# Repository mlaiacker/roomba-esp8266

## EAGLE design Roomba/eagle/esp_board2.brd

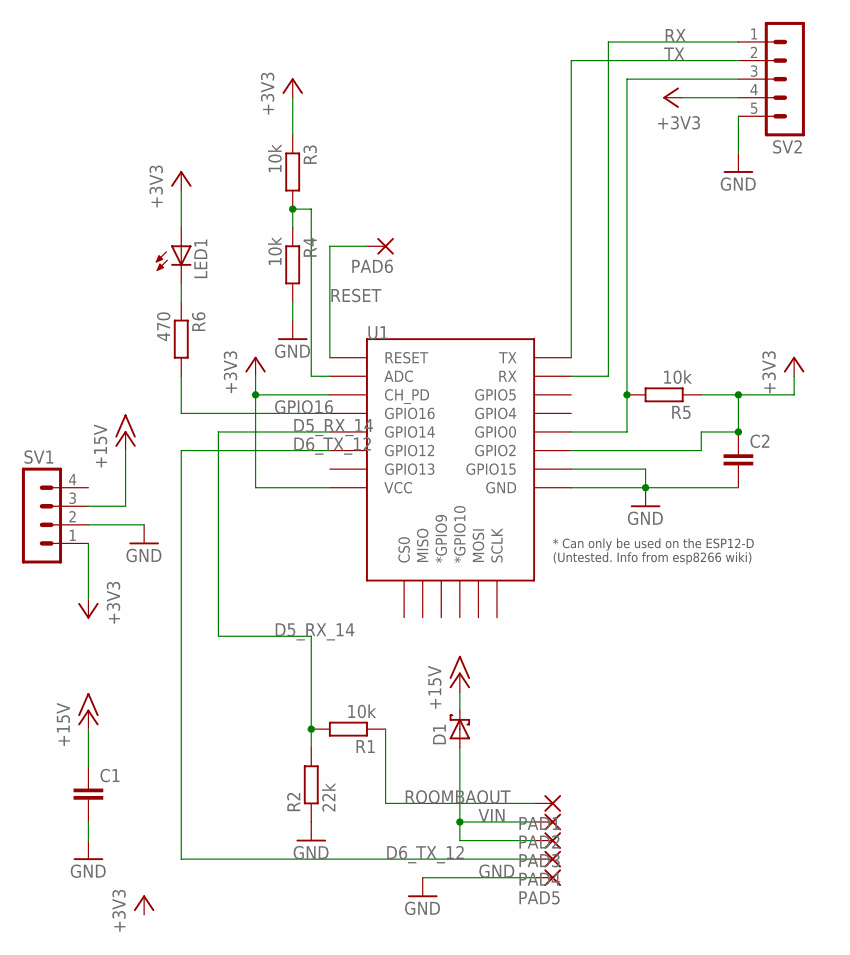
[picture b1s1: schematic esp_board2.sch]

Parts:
C1, C2: C-EUC3225; C3225
D1: SCHOTTKY-DIODESMC; SMC
LED1: LEDCHIP-LED0805; CHIP-LED0805
PAD1, PAD2, PAD3, PAD4, PAD5: 1,6/0,8
PAD6: SMD2; SMD1,27-2,54
R1, R3, R4, R5: 10k; R0805
R2: 22k; R0805
R6: 470; R0805
SV1: MA04-1
SV2: MA05-1
U1: ESP12ESMD; ESP12E-SMD

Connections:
+3V3: C2.1, LED1.A, R3.1, R5.1, SV1.1, SV2.4, U1.CH_PD, U1.GPIO2, U1.VCC
+15V: C1.1, D1.C, SV1.3
ADC: R3.2, R4.1, U1.ADC
D5_RX_14: R1.2, R2.2, U1.GPIO14
D6_TX_12: PAD4.1, U1.GPIO12
GND: C1.2, C2.2, PAD5.1, R2.1, R4.2, SV1.2, SV2.5, U1.GND, U1.GPIO15
GPIO0: R5.2, SV2.3, U1.GPIO0
GPIO16: R6.2, U1.GPIO16
unnamed: LED1.C, R6.1
RESET: PAD6.1, U1.RESET
ROOMBAOUT: PAD1.1, R1.1
RX: SV2.1, U1.RXD0 (RX)
TX: SV2.2, U1.TXD0 (TX)
VIN: D1.A, PAD2.1, PAD3.1

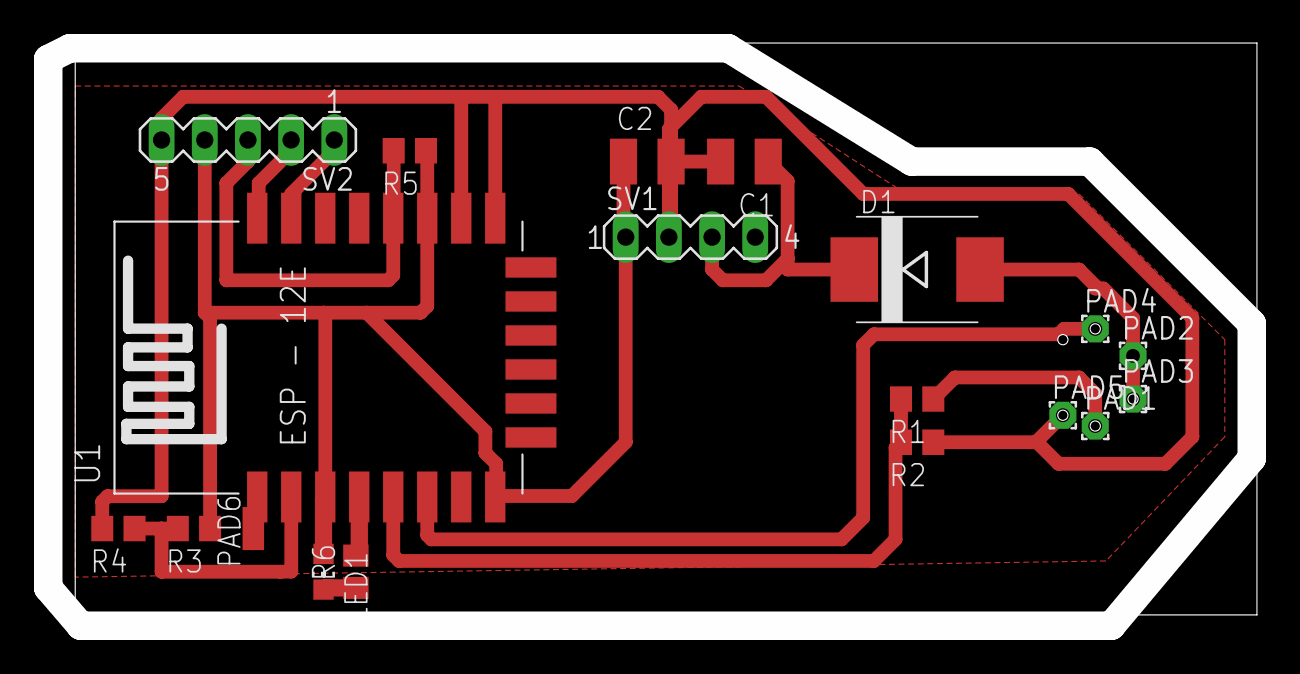
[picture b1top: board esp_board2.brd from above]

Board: 2 copper layers, 70.8 x 34.0 mm, 19 parts (0 on the bottom side), 14 nets.

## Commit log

2016-10-29 new features
2017-09-17 added other esp projects
2017-09-17 added led display to energy meter
2017-09-19 added a lot of json stuff esp-humid
2017-10-10 added logging to roombot and some cleanup
2018-06-18 humid for 3 pumps
2018-08-06 Add pump support with temperature compensation
2018-11-06 cleanup roomba now with new ntp server and new json lib and Sloeber project
2020-04-06 added esp motion
2020-04-06 motion sleep disable
2021-11-15 updated roomba with json api and cleaned up code
2021-11-15 removed led test
2021-11-15 added missing files
2021-11-15 added eagle files
2022-02-16 added gitignore and roomba update
2022-02-16 added wlan setting file example
